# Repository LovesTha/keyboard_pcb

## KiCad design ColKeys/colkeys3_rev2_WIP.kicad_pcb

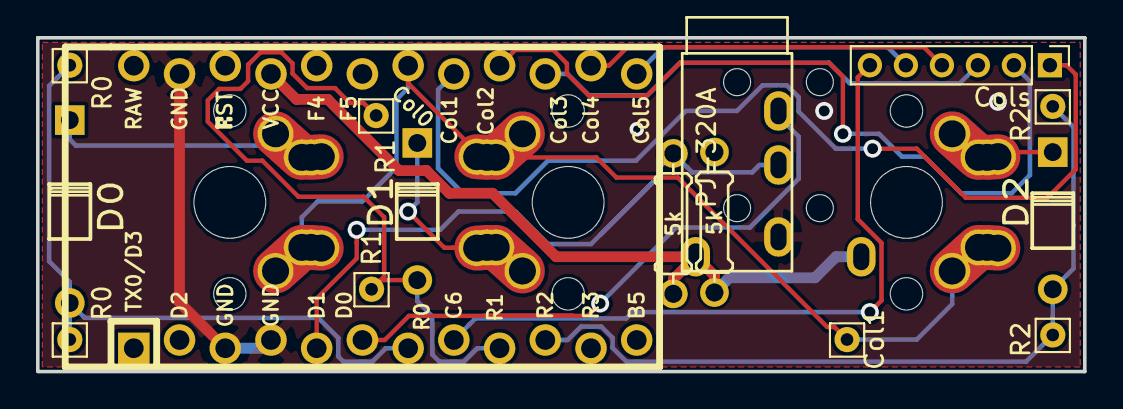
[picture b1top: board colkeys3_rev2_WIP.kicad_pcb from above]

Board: 2 copper layers, 58.2 x 18.5 mm, 18 parts (0 on the bottom side), 17 nets.

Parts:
Col1: Conn_01x01; Pin_D0.7mm_L6.5mm_W1.8mm_FlatFork
Cols: Conn_01x06; PinHeader_1x06_P2.00mm_Vertical
D0: D; Diode-Wide
D1, D2: D; Diode
K0, K1, K2: K34; Hybrid_PCB_100H_Dual_hole-flip
R0, R0#2, R1, R1#2, R2, R2#2: Conn_01x01; Pin_D0.7mm_L6.5mm_W1.8mm_FlatFork
R4, R5: 5k; Resistor-Compact
U1: ProMicro; ArduinoProMicro-ZigZag
U2: TRRS; TRRS-PJ-320A-dual

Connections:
Col0: Col1.1, K0.1, K1.1, K2.1, U1.18
Col1: Cols.1, U1.17
Col2: Cols.2, U1.16
Col3: Cols.3, U1.15
Col4: Cols.4, U1.14
Col5: Cols.5, U1.13
Col6: Cols.6, U1.8
GND: U1.3, U1.4, U1.23, U2.2
unnamed: D0.2, K0.2
unnamed: D1.2, K1.2
unnamed: D2.2, K2.2
Row0: D0.1, R0.1, R0#2.1, U1.7
Row1: D1.1, R1.1, R1#2.1, U1.9
Row2: D2.1, R2.1, R2#2.1, U1.10
SCL: R5.2, U1.5, U2.3
SDA: R4.2, U1.6, U2.4
VCC: R4.1, R5.1, U1.21, U2.1

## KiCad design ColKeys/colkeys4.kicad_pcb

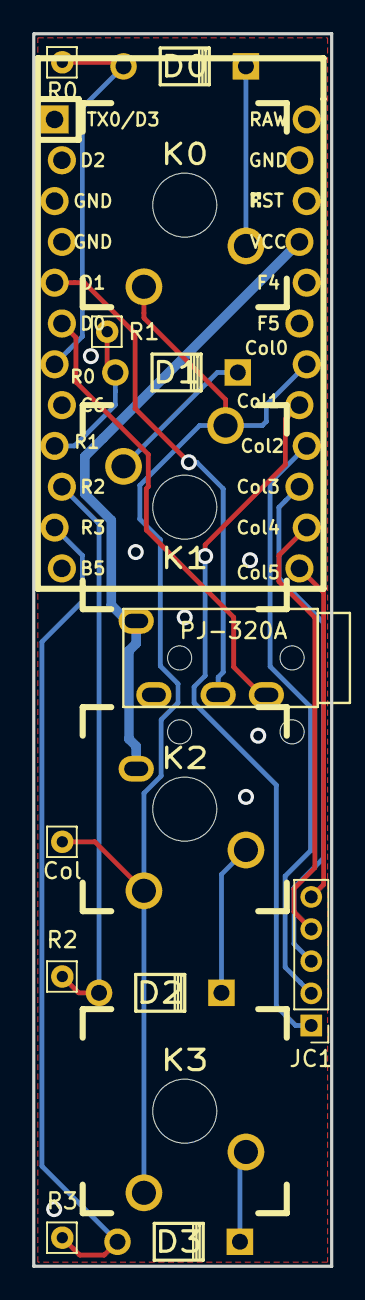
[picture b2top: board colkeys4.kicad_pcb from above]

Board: 2 copper layers, 18.5 x 76.7 mm, 16 parts (0 on the bottom side), 18 nets.

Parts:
Col: Conn_01x01; Pin_D0.7mm_L6.5mm_W1.8mm_FlatFork
D0, D1, D2, D3: D; Diode
JC1: Conn_01x05; PinHeader_1x05_P2.00mm_Vertical
K0, K1, K2, K3: K34; MX_Plate_100H
R0, R1, R2, R3: Conn_01x01; Pin_D0.7mm_L6.5mm_W1.8mm_FlatFork
U1: Elite-C; ArduinoProMicro-ZigZag
U2: TRRS; TRRS-PJ-320A-dual

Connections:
Col0: Col.1, K0.1, K1.1, K2.1, K3.1, U1.18
Col1: JC1.1, U1.17
Col2: JC1.2, U1.16
Col3: JC1.3, U1.15
Col4: JC1.4, U1.14
Col5: JC1.5, U1.13
GND: U1.3, U1.4, U1.23, U2.2
unnamed: D0.2, K0.2
unnamed: D1.2, K1.2
unnamed: D2.2, K2.2
unnamed: D3.2, K3.2
Row0: D0.1, R0.1, U1.7
Row1: D1.1, R1.1, U1.9
Row2: D2.1, R2.1, U1.10
Row3: D3.1, R3.1, U1.11
SCL: U1.5, U2.3
SDA: U1.6, U2.4
VCC: U1.21, U2.1

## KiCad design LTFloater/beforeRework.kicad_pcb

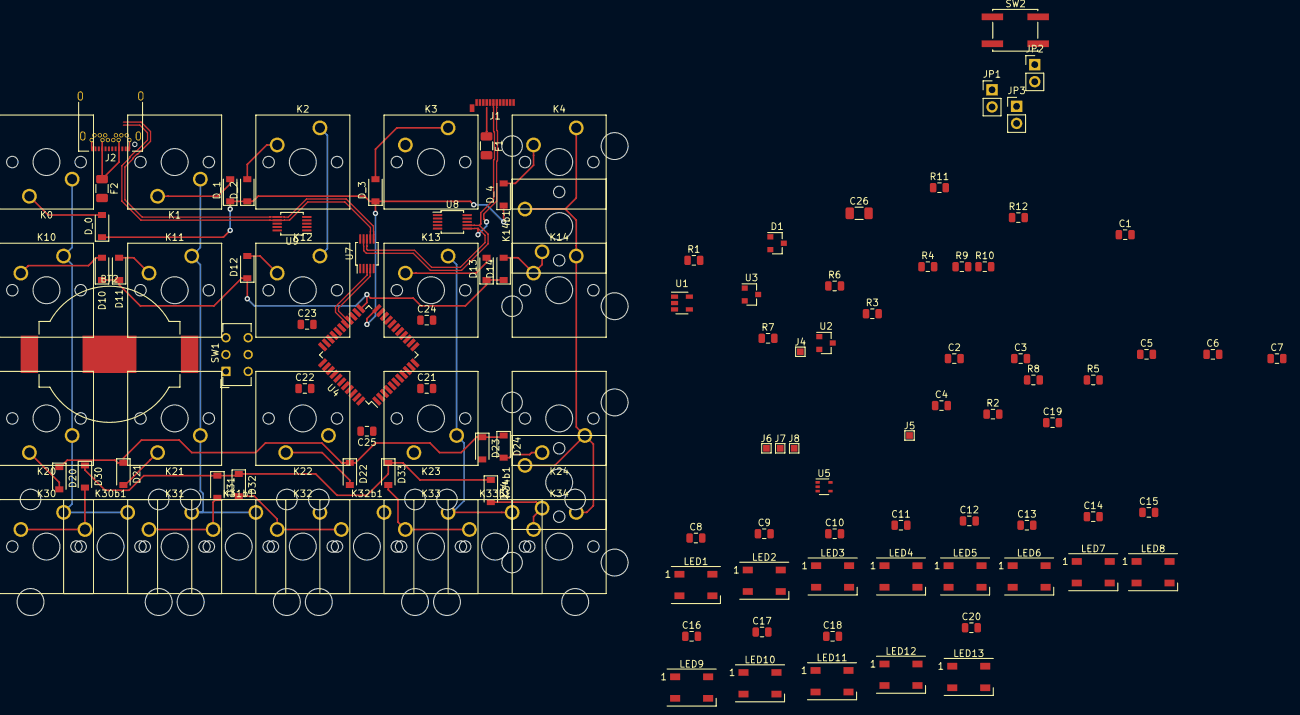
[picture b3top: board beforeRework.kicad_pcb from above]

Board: 2 copper layers, 121 parts (0 on the bottom side), 78 nets.

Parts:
BT2: Battery_Cell; BatteryHolder_MPD_BC2003_1x2032
C1, C2: 4.7uF; C_0805_2012Metric
C3, C4: 1uF; C_0805_2012Metric
C5, C6, C7, C8, C9, C10, C11, C12, C13, C14, C15, C16, C17, C18, C19, C20, C21, C22, C23, C24: 0.1uF; C_0805_2012Metric
C25: 10uF; C_0805_2012Metric
C26: 47uF; C_1206_3216Metric
D1: D_Schottky_x2_KCom_AAK; SOT-23
D10, D11, D12, D13, D14, D20, D21, D22, D23, D24, D30, D31, D32, D33, D34: D; D_SOD-123
D_0, D_1, D_2, D_3, D_4: D; D_SOD-123
F1, F2: Fuse; R_1206_3216Metric
J1: USB_C_Receptacle; USB_C_Plug_Molex_105444
J2: USB_C_Receptacle; USB_C_Receptacle_Amphenol_12401548E4-2A
J4: D4; TestPoint_Pad_1.0x1.0mm
J5: D5; TestPoint_Pad_1.0x1.0mm
J6: A6; TestPoint_Pad_1.0x1.0mm
J7: A7; TestPoint_Pad_1.0x1.0mm
J8: B0; TestPoint_Pad_1.0x1.0mm
JP1: NO USB; PinHeader_1x02_P2.54mm_Vertical
JP2: NO SW; PinHeader_1x02_P2.54mm_Vertical
JP3: BATT CHECK; PinHeader_1x02_P2.54mm_Vertical
K0: K00; SW_Cherry_MX1A_1.00u_PCB
K1: K01; SW_Cherry_MX1A_1.00u_PCB
K2: K02; SW_Cherry_MX1A_1.00u_PCB
K3: K03; SW_Cherry_MX1A_1.00u_PCB
K4: K04; SW_Cherry_MX1A_1.00u_PCB
K10: K10; SW_Cherry_MX1A_1.00u_PCB
K11: K11; SW_Cherry_MX1A_1.00u_PCB
K12: K12; SW_Cherry_MX1A_1.00u_PCB
K13: K13; SW_Cherry_MX1A_1.00u_PCB
K14: K14; SW_Cherry_MX1A_1.00u_PCB
K14b1: K14; SW_Cherry_MX1A_2.00u_PCB
K20: K20; SW_Cherry_MX1A_1.00u_PCB
K21: K21; SW_Cherry_MX1A_1.00u_PCB
K22: K22; SW_Cherry_MX1A_1.00u_PCB
K23: K23; SW_Cherry_MX1A_1.00u_PCB
K24: K24; SW_Cherry_MX1A_1.00u_PCB
K30: K30; SW_Cherry_MX1A_1.00u_PCB
K30b1: K30; SW_Cherry_MX1A_2.00u_PCB
K31: K31; SW_Cherry_MX1A_1.00u_PCB
K31b1: K31; SW_Cherry_MX1A_2.00u_PCB
K32: K32; SW_Cherry_MX1A_1.00u_PCB
K32b1: K32; SW_Cherry_MX1A_2.00u_PCB
K33: K33; SW_Cherry_MX1A_1.00u_PCB
K33b1: K33; SW_Cherry_MX1A_2.00u_PCB
K34: K34; SW_Cherry_MX1A_1.00u_PCB
K34b1: K34; SW_Cherry_MX1A_2.00u_PCB
LED1, LED2, LED3, LED4, LED5, LED6, LED7, LED8, LED9, LED10, LED11, LED12, LED13: WS2812B; LED_WS2812B_PLCC4_5.0x5.0mm_P3.2mm
R1, R6, R7, R8: 10k; R_0805_2012Metric
R2, R3: 470k; R_0805_2012Metric
R4, R5: 100k; R_0805_2012Metric
R9, R10, R11, R12: 5.1k; R_0805_2012Metric
SW1: Switch-6P-2S2T; SW_CuK_JS202011CQN_DPDT_Straight
SW2: SW_Push; SW_SPST_EVQQ2
U1: MCP73831; SOT-23-5
U2: MCP1700 (3.0V); SOT-23
U3: MCP1700 (3.3V); SOT-23
U4: ATXMEGA-A4U-EPAD; TQFP-44_10x10mm_P0.8mm
U5: 74LVC1G34; SOT-353_SC-70-5
U7, U8, U9: FSUSB42; MSOP-10_3x3mm_P0.5mm

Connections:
+3V3: C4.2, C5.1, C6.1, C7.1, R6.2, R7.1, U3.2, U7.1, U8.1, U9.1
+5V: C1.1, C8.1, C9.1, C10.1, C11.1, C12.1, C13.1, C14.1, C15.1, C16.1, C17.1, C18.1, C19.1, C20.1, F1.2, F2.2, LED1.1, LED2.1, LED3.1, LED4.1, LED5.1, LED6.1, LED7.1, LED8.1, LED9.1, LED10.1, LED11.1, LED12.1, LED13.1, R4.1, U1.4, U3.3, U5.5
+BATT: JP1.1, JP2.2, SW1.1, SW1.4
/A6: J6.1, U4.2
/A7: J7.1, U4.3
/B0: J8.1, U4.4
/BATT_IN: JP2.1, JP3.1, SW1.2, SW1.5, U2.2
/BAT_LI_ION: BT2.1, C2.1, R2.1, U1.3, U2.3
/BAT_LVL: JP3.2, R2.2, R3.1, U4.5
/BAT_PROG: R1.2, U4.12
/BAT_STAT: U1.1, U4.13
/D4: J4.1, U4.24
/D5: J5.1, U4.25
/D+: U4.27, U7.3
/D-: U4.26, U7.4
/I2C_LEFT: U4.36, U8.10
/I2C_RIGHT: U4.33, U9.10
/ROW0: D_0.1, D_1.1, D_2.1, D_3.1, D_4.1, U4.22
/ROW1: D10.1, D11.1, D12.1, D13.1, D14.1, U4.23
/ROW2: D20.1, D21.1, D22.1, D23.1, D24.1, U4.21
/ROW3: D30.1, D31.1, D32.1, D33.1, D34.1, U4.20
/RST: R8.2, SW2.2, U4.35
/SCL: R7.2, U4.29, U8.4, U9.4
/SDA: R6.1, U4.28, U8.3, U9.3
/UNDER_LED: U4.10, U5.2
/USB_L_D+: J1.A6, U7.9, U8.7
/USB_L_D-: J1.A7, U7.8, U8.6
/USB_OE: U4.37, U7.10
/USB_R_D+: J2.A6, J2.B6, U7.7, U9.7
/USB_R_D-: J2.A7, J2.B7, U7.6, U9.6
/USB_SEL: U4.32, U7.2
/VBUS_CHECK: R4.2, R5.1, U4.11
GND: BT2.2, C1.2, C2.2, C3.1, C4.1, C5.2, C6.2, C7.2, C8.2, C9.2, C10.2, C11.2, C12.2, C13.2, C14.2, C15.2, C16.2, C17.2, C18.2, C19.2, C20.2, C21.1, C22.1, C23.1, C24.1, C25.1, C26.1, J1.A1, J1.A12, J1.B1, J1.B12, J2.A1, J2.A12, J2.B1, J2.B12, LED1.3, LED2.3, LED3.3, LED4.3, LED5.3, LED6.3, LED7.3, LED8.3, LED9.3, LED10.3, LED11.3, LED12.3, LED13.3, R3.2, R5.2, R9.2, R10.2, R11.2, R12.2, SW2.1, U1.2, U2.1, U3.1, U4.8, U4.18, U4.30, U4.38, U5.3, U7.5, U8.2, U8.5, U9.2, U9.5
unnamed: D10.2, K10.2
unnamed: D11.2, K11.2
unnamed: D12.2, K12.2
unnamed: D13.2, K13.2
unnamed: D14.2, K14.2, K14b1.2
unnamed: D20.2, K20.1
unnamed: D21.2, K21.1
unnamed: D22.2, K22.1
unnamed: D23.2, K23.1
unnamed: D24.2, K24.1
unnamed: D30.2, K30.2, K30b1.2
unnamed: D31.2, K31.2, K31b1.2
unnamed: D32.2, K32.2, K32b1.2
unnamed: D33.2, K33.2, K33b1.2
unnamed: D34.2, K34.2, K34b1.2
unnamed: D_0.2, K0.1
unnamed: D_1.2, K1.1
unnamed: D_2.2, K2.2
unnamed: D_3.2, K3.1
unnamed: D_4.2, K4.2
unnamed: J1.A5, R9.1
unnamed: J1.B3, J1.B5, R10.1
unnamed: J2.A5, R11.1
unnamed: J2.B3, J2.B5, R12.1
unnamed: K0.2, K10.1, K20.2, K30.1, K30b1.1
unnamed: K1.2, K11.1, K21.2, K31.1, K31b1.1
unnamed: K2.1, K12.1, K22.2, K32.1, K32b1.1
unnamed: K3.2, K13.1, K23.2, K33.1, K33b1.1
unnamed: K4.1, K14.1, K14b1.1, K24.2, K34.1, K34b1.1
unnamed: LED1.2, LED2.4
unnamed: LED1.4, U5.4
unnamed: LED2.2, LED3.4
unnamed: LED3.2, LED4.4
unnamed: LED4.2, LED5.4
unnamed: LED5.2, LED6.4
unnamed: LED6.2, LED7.4
unnamed: LED7.2, LED8.4
unnamed: LED8.2, LED9.4
unnamed: LED10.2, LED11.4
unnamed: LED9.2, LED10.4
unnamed: LED11.2, LED12.4
unnamed: LED12.2, LED13.4
unnamed: R1.1, U1.5
VBUS: F1.1, F2.1, J1.A4, J1.A9, J1.B4, J1.B9, J2.A4, J2.A9, J2.B4, J2.B9
VCC: C21.2, C22.2, C23.2, C24.2, C25.2, C26.2, JP1.2, R8.1, U4.9, U4.19, U4.31, U4.39
